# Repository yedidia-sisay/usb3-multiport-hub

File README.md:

# usb3-multiport-hub

An open-source USB 3.2 Gen 2 (10 Gbps) multiport hub & docking station — designed in KiCad 10.

## Overview

A compact (93 × 69 mm), 6-layer PCB that combines a high-speed USB hub, video output, and a card reader into a single board. Powered by a 12V DC input with an onboard 20A buck converter.

### Features

| Feature | Details |
|---|---|
| **Hub IC** | Microchip USB7216CT — USB 3.2 Gen 2 SmartHub, 10 Gbps |
| **Upstream** | USB Type-C with HD3SS3220 CC controller & 10G mux |
| **Downstream Port 1** | USB Type-C (10 Gbps + USB 2.0) |
| **Downstream Port 2** | USB 3.0 Type-A (10 Gbps + USB 2.0) |
| **SD Card Reader** | MicroSD/TF via Genesys Logic GL3224 |
| **HDMI Output** | USB 3.0 → HDMI via MacroSilicon MS9132 + 64Mbit SPI Flash |
| **Power Input** | 12V DC barrel jack (5.5 × 2.1 mm) |
| **ESD Protection** | TI TPD4E05U06 & TPD4E02B04 on all external ports |
| **PCB** | 6-layer, 93 × 69 mm, controlled impedance (90Ω USB, 100Ω HDMI) |

## Block Diagram

```
                    ┌──────────────────────────────────────┐
                    │         Microchip USB7216CT          │
  USB-C ─── HD3SS3220 ──▶ Upstream                        │
  (10G Mux)         │                                      │
                    │   Port 1 ──▶ USB-C Downstream        │
                    │   Port 2 ──▶ USB-A 3.0 Downstream    │
                    │   Port 3 ──▶ GL3224 ──▶ MicroSD Slot │
                    │   Port 4 ──▶ MS9132 ──▶ HDMI Output  │
                    └──────────────────────────────────────┘

  12V DC ──▶ TPS53353 (20A Buck) ──▶ +5V ──┬──▶ SGM61020 ──▶ +3.3V
                                            ├──▶ SGM61020 ──▶ +1.15V
                                            └──▶ TPS79325 ──▶ +2.5V (LDO)
```

## Schematic Hierarchy

| Sheet | Description |
|---|---|
| `usb_hub_2.kicad_sch` | Top-level sheet with hierarchy |
| `hub.kicad_sch` | USB7216 hub IC, crystal, decoupling |
| `upport.kicad_sch` | Upstream USB-C port with HD3SS3220 mux |
| `PORT1.kicad_sch` | Downstream USB-C port 1 |
| `port23.kicad_sch` | Downstream USB-A port 2 + GL3224 SD card reader |
| `port_4_5.kicad_sch` | MS9132 HDMI output + SPI flash |
| `power.kicad_sch` | Full power tree (12V → 5V/3.3V/1.15V/2.5V) |

## Key Components

| Part | Manufacturer | Description |
|---|---|---|
| USB7216CT/KDX | Microchip | USB 3.2 Gen 2 10Gbps SmartHub (VQFN-100) |
| HD3SS3220RNHR | Texas Instruments | USB-C DRP controller + 10G mux (WQFN-30) |
| GL3224-OIY04 | Genesys Logic | USB 3.0 SD/MMC card reader (QFN-64) |
| MS9132 | MacroSilicon | USB 3.0 → HDMI display adapter (QFN-64) |
| W25Q64JVSSIQ | Winbond | 64Mbit SPI Flash for MS9132 firmware |
| TPS53353DQPR | Texas Instruments | 20A synchronous buck converter, 12V→5V |
| SGM61020XN5G/TR | SG Micro | 2A synchronous buck converter (×2) |
| TPS79325DBVR | Texas Instruments | 200mA ultra-low-noise 2.5V LDO |
| AON7405 | Alpha & Omega Semi | 30V P-MOSFET for reverse polarity protection |
| AP22615BWU-7 | Diodes Inc | USB power distribution switch (×2) |
| TPD4E05U06 / TPD4E02B04 | Texas Instruments | 4-ch ultra-low capacitance ESD protection |

## PCB Stackup

| Layer | Function |
|---|---|
| L1 — F.Cu | Top signal (high-speed differential pairs) |
| L2 — In1.Cu | Solid GND reference plane |
| L3 — In2.Cu | Internal signal routing |
| L4 — In3.Cu | Power planes (+5V, +12V, +3.3V) |
| L5 — In4.Cu | GND plane |
| L6 — B.Cu | Bottom signal |

**Impedance-controlled netclasses:**
- `USB_90R` — 90 Ω differential (0.136 mm trace / 0.15 mm gap)
- `HDMI_100R` — 100 Ω differential (0.09 mm trace / 0.09 mm gap)
- `CLOCK` — 0.15 mm trace, 0.30 mm clearance
- `POWER` — 0.50 mm trace

## Repository Structure

```
usb3-multiport-hub/
├── usb_hub_2.kicad_pro          # KiCad project file
├── usb_hub_2.kicad_sch          # Top-level schematic
├── usb_hub_2.kicad_pcb          # PCB layout
├── usb_hub_2.kicad_dru          # Design rules
├── hub.kicad_sch                # Hub IC sheet
├── upport.kicad_sch             # Upstream USB-C port sheet
├── PORT1.kicad_sch              # Downstream USB-C port sheet
├── port23.kicad_sch             # Downstream USB-A + SD reader sheet
├── port_4_5.kicad_sch           # HDMI output sheet
├── power.kicad_sch              # Power supply sheet
├── custom_libs/
│   ├── local_parts.kicad_sym    # Custom schematic symbols
│   ├── local_parts.pretty/      # Custom PCB footprints (25)
│   └── local_parts.3dshapes/    # 3D models (STEP + WRL)
├── docs/                        # Datasheets & reference designs
├── images/                      # Board renders & schematics
└── output/                      # Manufacturing outputs (gerbers, BOM)
```

## Getting Started

### Opening the Project

1. Clone this repository
2. Open `usb_hub_2.kicad_pro` in KiCad
3. All custom libraries are project-relative — no additional library setup needed

### Manufacturing

The board is designed for standard 6-layer PCB fabrication with controlled impedance. Export Gerbers and drill files from KiCad to the `output/` directory.

## Design References

The `docs/` directory contains the key reference documents used during design:

- **USB7216 Datasheet** (DS00003143B)
- **USB7216 Hardware Design Checklist** (AN3286)
- **USB72x6 / USB7252 Errata** (80000847C)
- **USB7216 Evaluation Board Schematic**

## Status

> **⚠️ Work in Progress** — This design is under active development. DRC cleanup and manufacturing output generation are pending.

## License

This project is open-source hardware. See [LICENSE](LICENSE) for details.

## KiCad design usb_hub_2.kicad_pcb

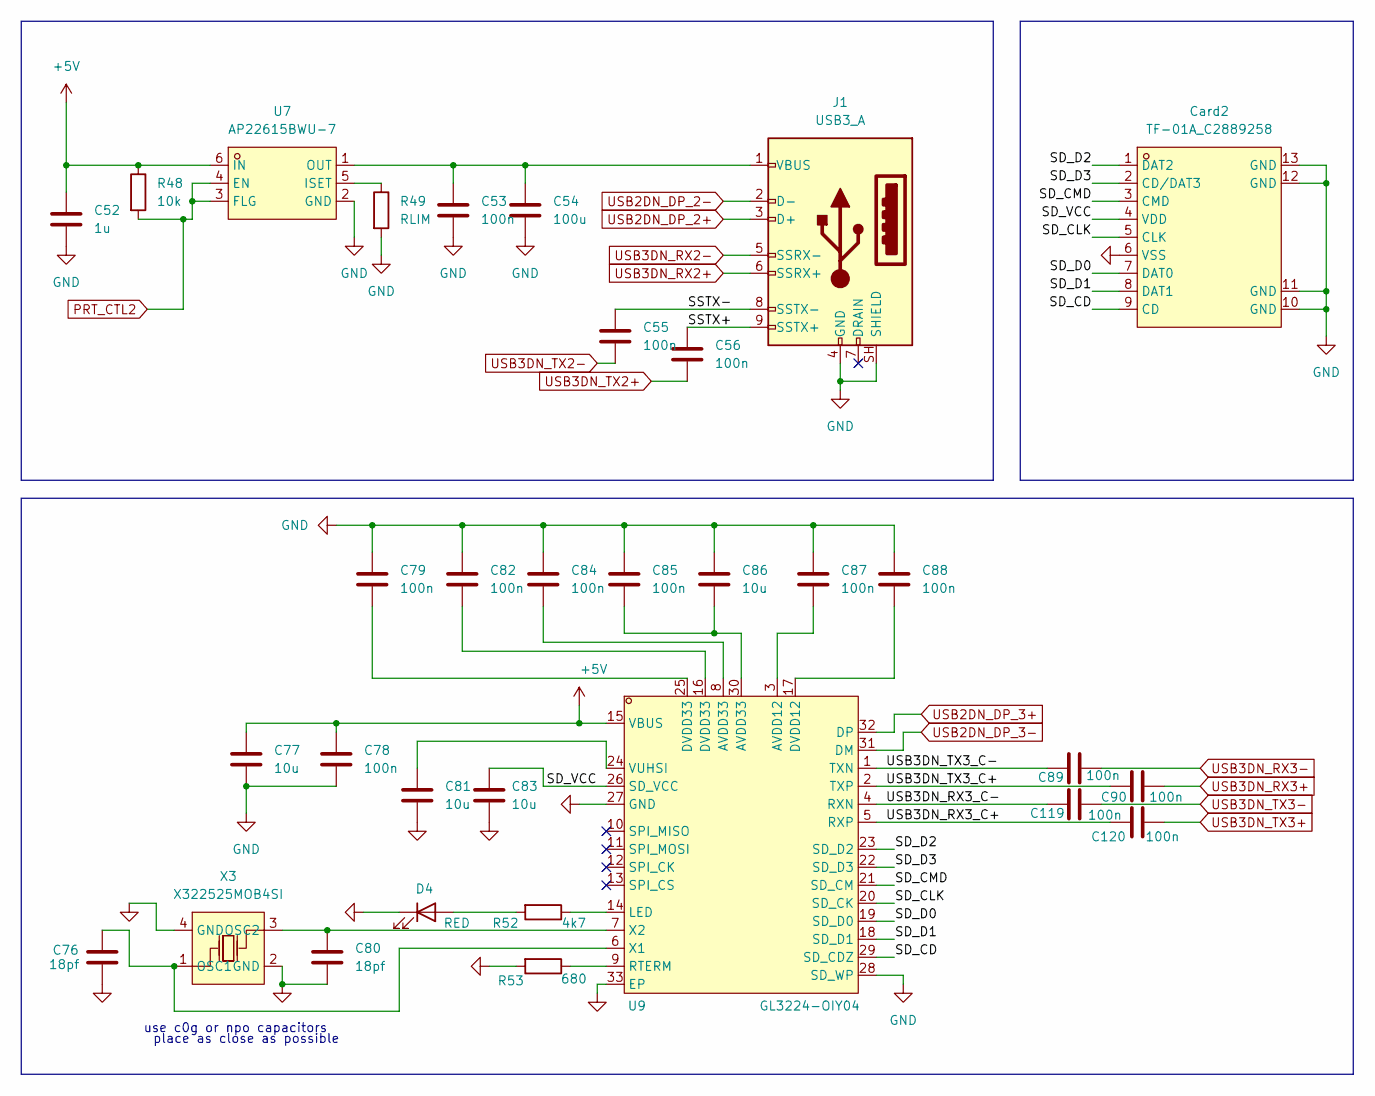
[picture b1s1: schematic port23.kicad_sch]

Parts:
C52: 1u; C_0402_1005Metric
C53, C55, C56, C78, C79, C82, C84, C85, C87, C88, C89, C90, C119, C120: 100n; C_0402_1005Metric
C54: 100u; C_0402_1005Metric
C76, C80: 18pf; C_0402_1005Metric
C77: 10u; C_0805_2012Metric
C81, C83, C86: 10u; C_0402_1005Metric
Card2: TF-01A_C2889258; TF-SMD_TF-02; MPN TF-01A; LCSC Part C2889258
D4: RED; LED_0402_1005Metric
J1: USB3_A; USB3_A_Receptacle_Wuerth_692122030100
R48: 10k; R_0402_1005Metric
R49: RLIM; R_0402_1005Metric
R52: 4k7; R_0402_1005Metric
R53: 680; R_0402_1005Metric
U7: AP22615BWU-7; TSOT-26_L2.9-W1.6-P0.95-LS2.8-BL; MPN AP22615BWU-7; LCSC Part C2150284
U9: GL3224-OIY04; HQFN-32_L5.0-W5.0-P0.50-BL-EP3.0; MPN GL3224-OIY04; LCSC Part C157357
X3: X322525MOB4SI; CRYSTAL-SMD_4P-L3.2-W2.5-BL; MPN X322525MOB4SI; LCSC Part C9006

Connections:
+5V: C52.1, C77.2, C78.2, R48.1, U7.6 (IN), U9.15 (VBUS); also elsewhere on the board
/PORT23/SD_CD: Card2.9 (CD), U9.29 (SD_CDZ)
/PORT23/SD_CLK: Card2.5 (CLK), U9.20 (SD_CK)
/PORT23/SD_CMD: Card2.3 (CMD), U9.21 (SD_CM)
/PORT23/SD_D0: Card2.7 (DAT0), U9.19 (SD_D0)
/PORT23/SD_D1: Card2.8 (DAT1), U9.18 (SD_D1)
/PORT23/SD_D2: Card2.1 (DAT2), U9.23 (SD_D2)
/PORT23/SD_D3: Card2.2 (CD/DAT3), U9.22 (SD_D3)
/PORT23/SD_VCC: C83.2, Card2.4 (VDD), U9.26 (SD_VCC)
/PORT23/SSTX+: C56.1, J1.9 (SSTX+)
/PORT23/SSTX-: C55.1, J1.8 (SSTX-)
/PORT23/USB3DN_RX3_C+: C120.1, U9.5 (RXP)
/PORT23/USB3DN_RX3_C-: C119.1, U9.4 (RXN)
/PORT23/USB3DN_TX3_C+: C90.1, U9.2 (TXP)
/PORT23/USB3DN_TX3_C-: C89.1, U9.1 (TXN)
GND: C52.2, C53.2, C54.2, C76.2, C77.1, C78.1, C79.2, C80.2, C81.1, C82.2, C83.1, C84.2, C85.2, C86.2, C87.2, C88.2, Card2.6 (VSS), Card2.10 (GND), Card2.11 (GND), Card2.12 (GND), Card2.13 (GND), D4.1 (K), J1.4 (GND), J1.SH (SHIELD), R49.2, R53.2, U7.2 (GND), U9.27 (GND), U9.28 (SD_WP), U9.33 (EP), X3.2 (GND), X3.4 (GND); also elsewhere on the board
unnamed: C79.1, U9.25 (DVDD33)
unnamed: C82.1, U9.16 (DVDD33)
unnamed: C84.1, U9.8 (AVDD33)
unnamed: C85.1, C86.1, U9.30 (AVDD33)
unnamed: D4.2 (A), R52.2
unnamed: C53.1, C54.1, J1.1 (VBUS), U7.1 (OUT)
unnamed: R49.1, U7.5 (ISET)
unnamed: C87.1, U9.3 (AVDD12)
unnamed: C88.1, U9.17 (DVDD12)
unnamed: R52.1, U9.14 (LED)
unnamed: R53.1, U9.9 (RTERM)
unnamed: C81.2, U9.24 (VUHSI)
unnamed: C76.1, U9.6 (X1), X3.1 (OSC1)
unnamed: C80.1, U9.7 (X2), X3.3 (OSC2)
PRT_CTL2: R48.2, U7.3 (FLG), U7.4 (EN); also elsewhere on the board
USB2DN_DP_2+: J1.3 (D+); also elsewhere on the board
USB2DN_DP_2-: J1.2 (D-); also elsewhere on the board
USB2DN_DP_3+: U9.32 (DP); also elsewhere on the board
USB2DN_DP_3-: U9.31 (DM); also elsewhere on the board
USB3DN_RX2+: J1.6 (SSRX+); also elsewhere on the board
USB3DN_RX2-: J1.5 (SSRX-); also elsewhere on the board
USB3DN_RX3+: C90.2; also elsewhere on the board
USB3DN_RX3-: C89.2; also elsewhere on the board
USB3DN_TX2+: C56.2; also elsewhere on the board
USB3DN_TX2-: C55.2; also elsewhere on the board
USB3DN_TX3+: C120.2; also elsewhere on the board
USB3DN_TX3-: C119.2; also elsewhere on the board

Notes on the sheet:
place as close as possible
use c0g or npo capacitors

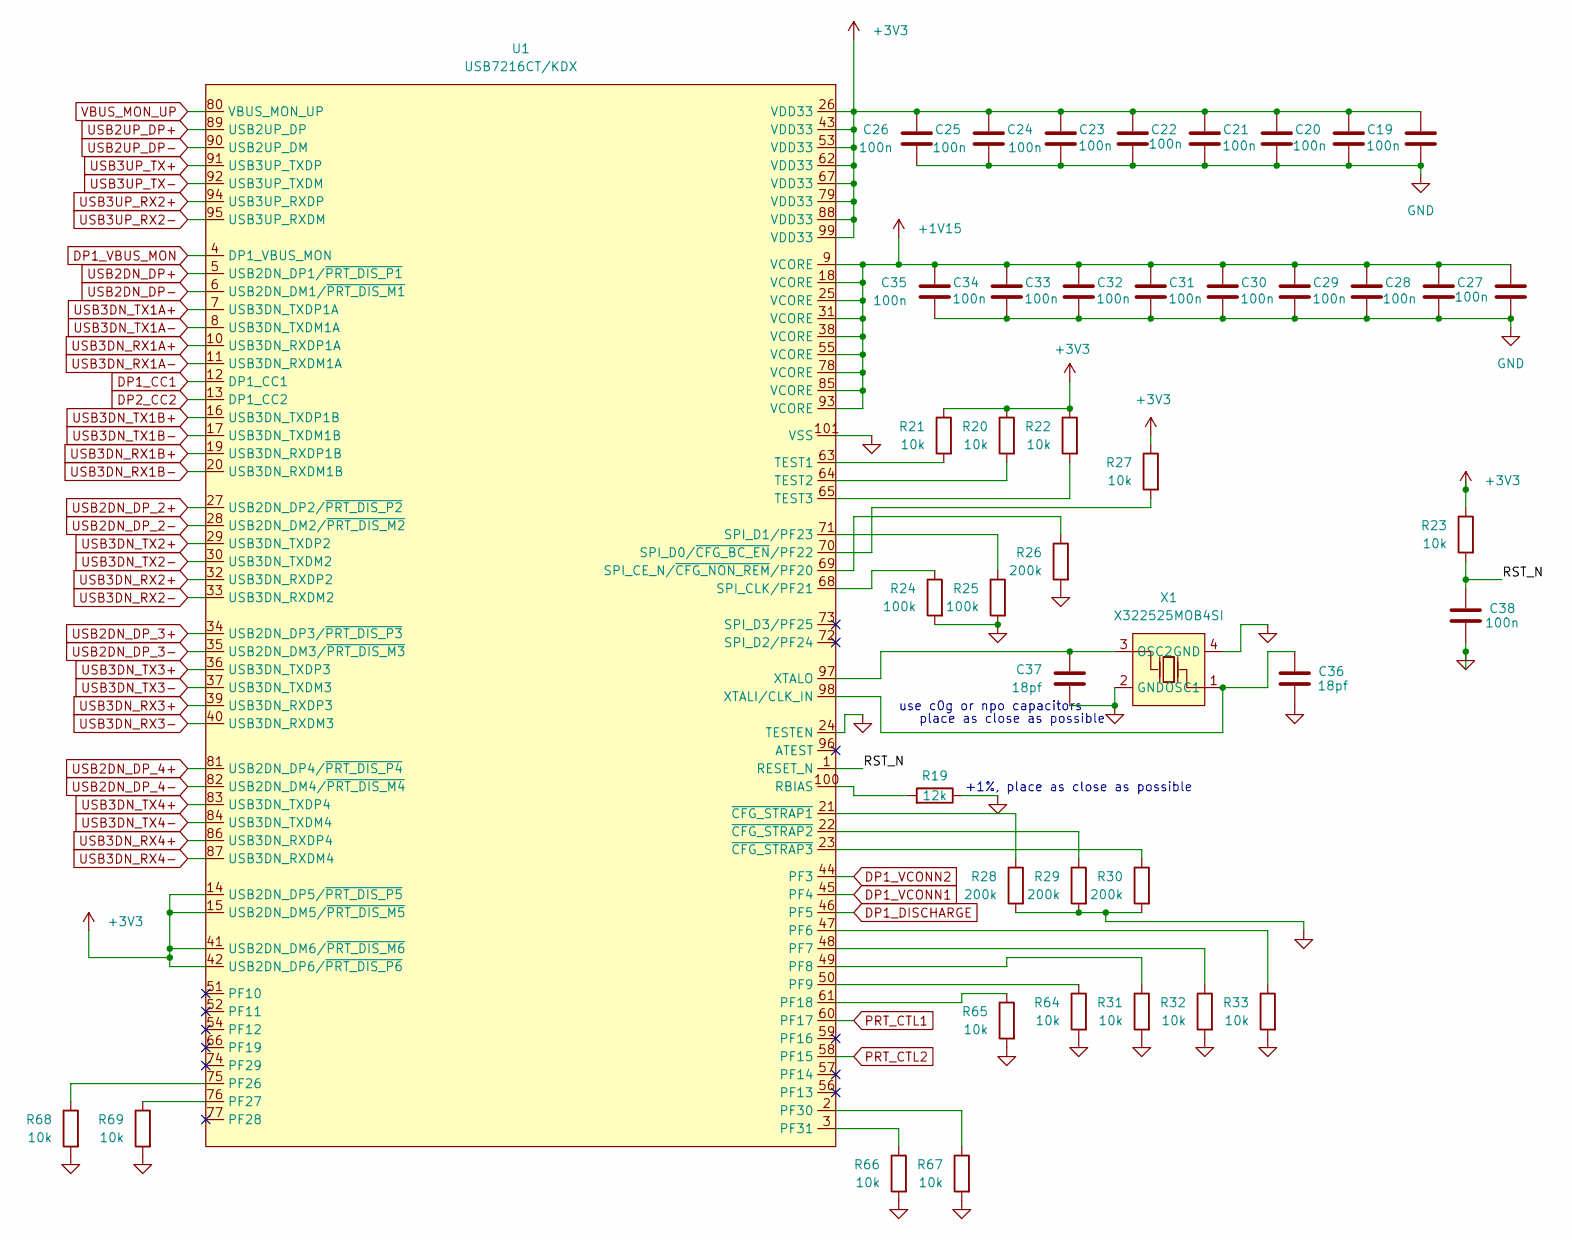
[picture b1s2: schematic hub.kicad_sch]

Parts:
C19, C20, C21, C22, C23, C24, C25, C26, C27, C28, C29, C30, C31, C32, C33, C34, C35, C38: 100n; C_0402_1005Metric
C36, C37: 18pf; C_0402_1005Metric
R19: 12k; R_0402_1005Metric
R20, R21, R22, R23, R27, R31, R32, R33, R64, R65, R66, R67, R68, R69: 10k; R_0402_1005Metric
R24, R25: 100k; R_0402_1005Metric
R26, R28, R29, R30: 200k; R_0402_1005Metric
U1: USB7216CT/KDX; VQFN-100_L12.0-W12.0-P0.40-TL-EP8.0; MPN USB7216CT/KDX; LCSC Part C3210684
X1: X322525MOB4SI; CRYSTAL-SMD_4P-L3.2-W2.5-BL; MPN X322525MOB4SI; LCSC Part C9006

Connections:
+1V15: C27.1, C28.1, C29.1, C30.1, C31.1, C32.1, C33.1, C34.1, C35.1, U1.9 (VCORE), U1.18 (VCORE), U1.25 (VCORE), U1.31 (VCORE), U1.38 (VCORE), U1.55 (VCORE), U1.78 (VCORE), U1.85 (VCORE), U1.93 (VCORE); also elsewhere on the board
+3V3: C19.1, C20.1, C21.1, C22.1, C23.1, C24.1, C25.1, C26.1, R20.1, R21.1, R22.1, R23.1, R27.1, U1.14 (USB2DN_DP5/~PRT_DIS_P5), U1.15 (USB2DN_DM5/~PRT_DIS_M5), U1.26 (VDD33), U1.41 (USB2DN_DM6/~PRT_DIS_M6), U1.42 (USB2DN_DP6/~PRT_DIS_P6), U1.43 (VDD33), U1.53 (VDD33), U1.62 (VDD33), U1.67 (VDD33), U1.79 (VDD33), U1.88 (VDD33), U1.99 (VDD33); also elsewhere on the board
/HUB/RST_N: C38.1, R23.2, U1.1 (RESET_N)
DP1_CC1: U1.12 (DP1_CC1); also elsewhere on the board
DP1_DISCHARGE: U1.46 (PF5); also elsewhere on the board
DP1_VBUS_MON: U1.4 (DP1_VBUS_MON); also elsewhere on the board
DP1_VCONN1: U1.45 (PF4); also elsewhere on the board
DP1_VCONN2: U1.44 (PF3); also elsewhere on the board
DP2_CC2: U1.13 (DP1_CC2); also elsewhere on the board
GND: C19.2, C20.2, C21.2, C22.2, C23.2, C24.2, C25.2, C26.2, C27.2, C28.2, C29.2, C30.2, C31.2, C32.2, C33.2, C34.2, C35.2, C36.2, C37.2, C38.2, R19.1, R24.2, R25.2, R26.2, R28.2, R29.2, R30.2, R31.2, R32.2, R33.2, R64.2, R65.2, R66.2, R67.2, R68.2, R69.2, U1.24 (TESTEN), U1.101 (VSS), X1.2 (GND), X1.4 (GND); also elsewhere on the board
unnamed: R33.1, U1.47 (PF6)
unnamed: R32.1, U1.48 (PF7)
unnamed: R31.1, U1.49 (PF8)
unnamed: R64.1, U1.50 (PF9)
unnamed: R65.1, U1.61 (PF18)
unnamed: R68.1, U1.75 (PF26)
unnamed: R69.1, U1.76 (PF27)
unnamed: R67.1, U1.2 (PF30)
unnamed: R66.1, U1.3 (PF31)
unnamed: R19.2, U1.100 (RBIAS)
unnamed: R26.1, U1.69 (SPI_CE_N/~CFG_NON_REM/PF20)
unnamed: R24.1, U1.68 (SPI_CLK/PF21)
unnamed: R27.2, U1.70 (SPI_D0/~CFG_BC_EN/PF22)
unnamed: R25.1, U1.71 (SPI_D1/PF23)
unnamed: R21.2, U1.63 (TEST1)
unnamed: R20.2, U1.64 (TEST2)
unnamed: R22.2, U1.65 (TEST3)
unnamed: C36.1, U1.98 (XTALI/CLK_IN), X1.1 (OSC1)
unnamed: C37.1, U1.97 (XTALO), X1.3 (OSC2)
unnamed: R28.1, U1.21 (~CFG_STRAP1)
unnamed: R29.1, U1.22 (~CFG_STRAP2)
unnamed: R30.1, U1.23 (~CFG_STRAP3)
PRT_CTL1: U1.60 (PF17); also elsewhere on the board
PRT_CTL2: U1.58 (PF15); also elsewhere on the board
USB2DN_DP+: U1.5 (USB2DN_DP1/~PRT_DIS_P1); also elsewhere on the board
USB2DN_DP-: U1.6 (USB2DN_DM1/~PRT_DIS_M1); also elsewhere on the board
USB2DN_DP_2+: U1.27 (USB2DN_DP2/~PRT_DIS_P2); also elsewhere on the board
USB2DN_DP_2-: U1.28 (USB2DN_DM2/~PRT_DIS_M2); also elsewhere on the board
USB2DN_DP_3+: U1.34 (USB2DN_DP3/~PRT_DIS_P3); also elsewhere on the board
USB2DN_DP_3-: U1.35 (USB2DN_DM3/~PRT_DIS_M3); also elsewhere on the board
USB2DN_DP_4+: U1.81 (USB2DN_DP4/~PRT_DIS_P4); also elsewhere on the board
USB2DN_DP_4-: U1.82 (USB2DN_DM4/~PRT_DIS_M4); also elsewhere on the board
USB2UP_DP+: U1.89 (USB2UP_DP); also elsewhere on the board
USB2UP_DP-: U1.90 (USB2UP_DM); also elsewhere on the board
USB3DN_RX1A+: U1.10 (USB3DN_RXDP1A); also elsewhere on the board
USB3DN_RX1A-: U1.11 (USB3DN_RXDM1A); also elsewhere on the board
USB3DN_RX1B+: U1.19 (USB3DN_RXDP1B); also elsewhere on the board
USB3DN_RX1B-: U1.20 (USB3DN_RXDM1B); also elsewhere on the board
USB3DN_RX2+: U1.32 (USB3DN_RXDP2); also elsewhere on the board
USB3DN_RX2-: U1.33 (USB3DN_RXDM2); also elsewhere on the board
USB3DN_RX3+: U1.39 (USB3DN_RXDP3); also elsewhere on the board
USB3DN_RX3-: U1.40 (USB3DN_RXDM3); also elsewhere on the board
USB3DN_RX4+: U1.86 (USB3DN_RXDP4); also elsewhere on the board
USB3DN_RX4-: U1.87 (USB3DN_RXDM4); also elsewhere on the board
USB3DN_TX1A+: U1.7 (USB3DN_TXDP1A); also elsewhere on the board
USB3DN_TX1A-: U1.8 (USB3DN_TXDM1A); also elsewhere on the board
USB3DN_TX1B+: U1.16 (USB3DN_TXDP1B); also elsewhere on the board
USB3DN_TX1B-: U1.17 (USB3DN_TXDM1B); also elsewhere on the board
USB3DN_TX2+: U1.29 (USB3DN_TXDP2); also elsewhere on the board
USB3DN_TX2-: U1.30 (USB3DN_TXDM2); also elsewhere on the board
USB3DN_TX3+: U1.36 (USB3DN_TXDP3); also elsewhere on the board
USB3DN_TX3-: U1.37 (USB3DN_TXDM3); also elsewhere on the board
USB3DN_TX4+: U1.83 (USB3DN_TXDP4); also elsewhere on the board
USB3DN_TX4-: U1.84 (USB3DN_TXDM4); also elsewhere on the board
USB3UP_RX2+: U1.94 (USB3UP_RXDP); also elsewhere on the board
USB3UP_RX2-: U1.95 (USB3UP_RXDM); also elsewhere on the board
USB3UP_TX+: U1.91 (USB3UP_TXDP); also elsewhere on the board
USB3UP_TX-: U1.92 (USB3UP_TXDM); also elsewhere on the board
VBUS_MON_UP: U1.80 (VBUS_MON_UP); also elsewhere on the board

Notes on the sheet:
+1%, place as close as possible
place as close as possible
use c0g or npo capacitors

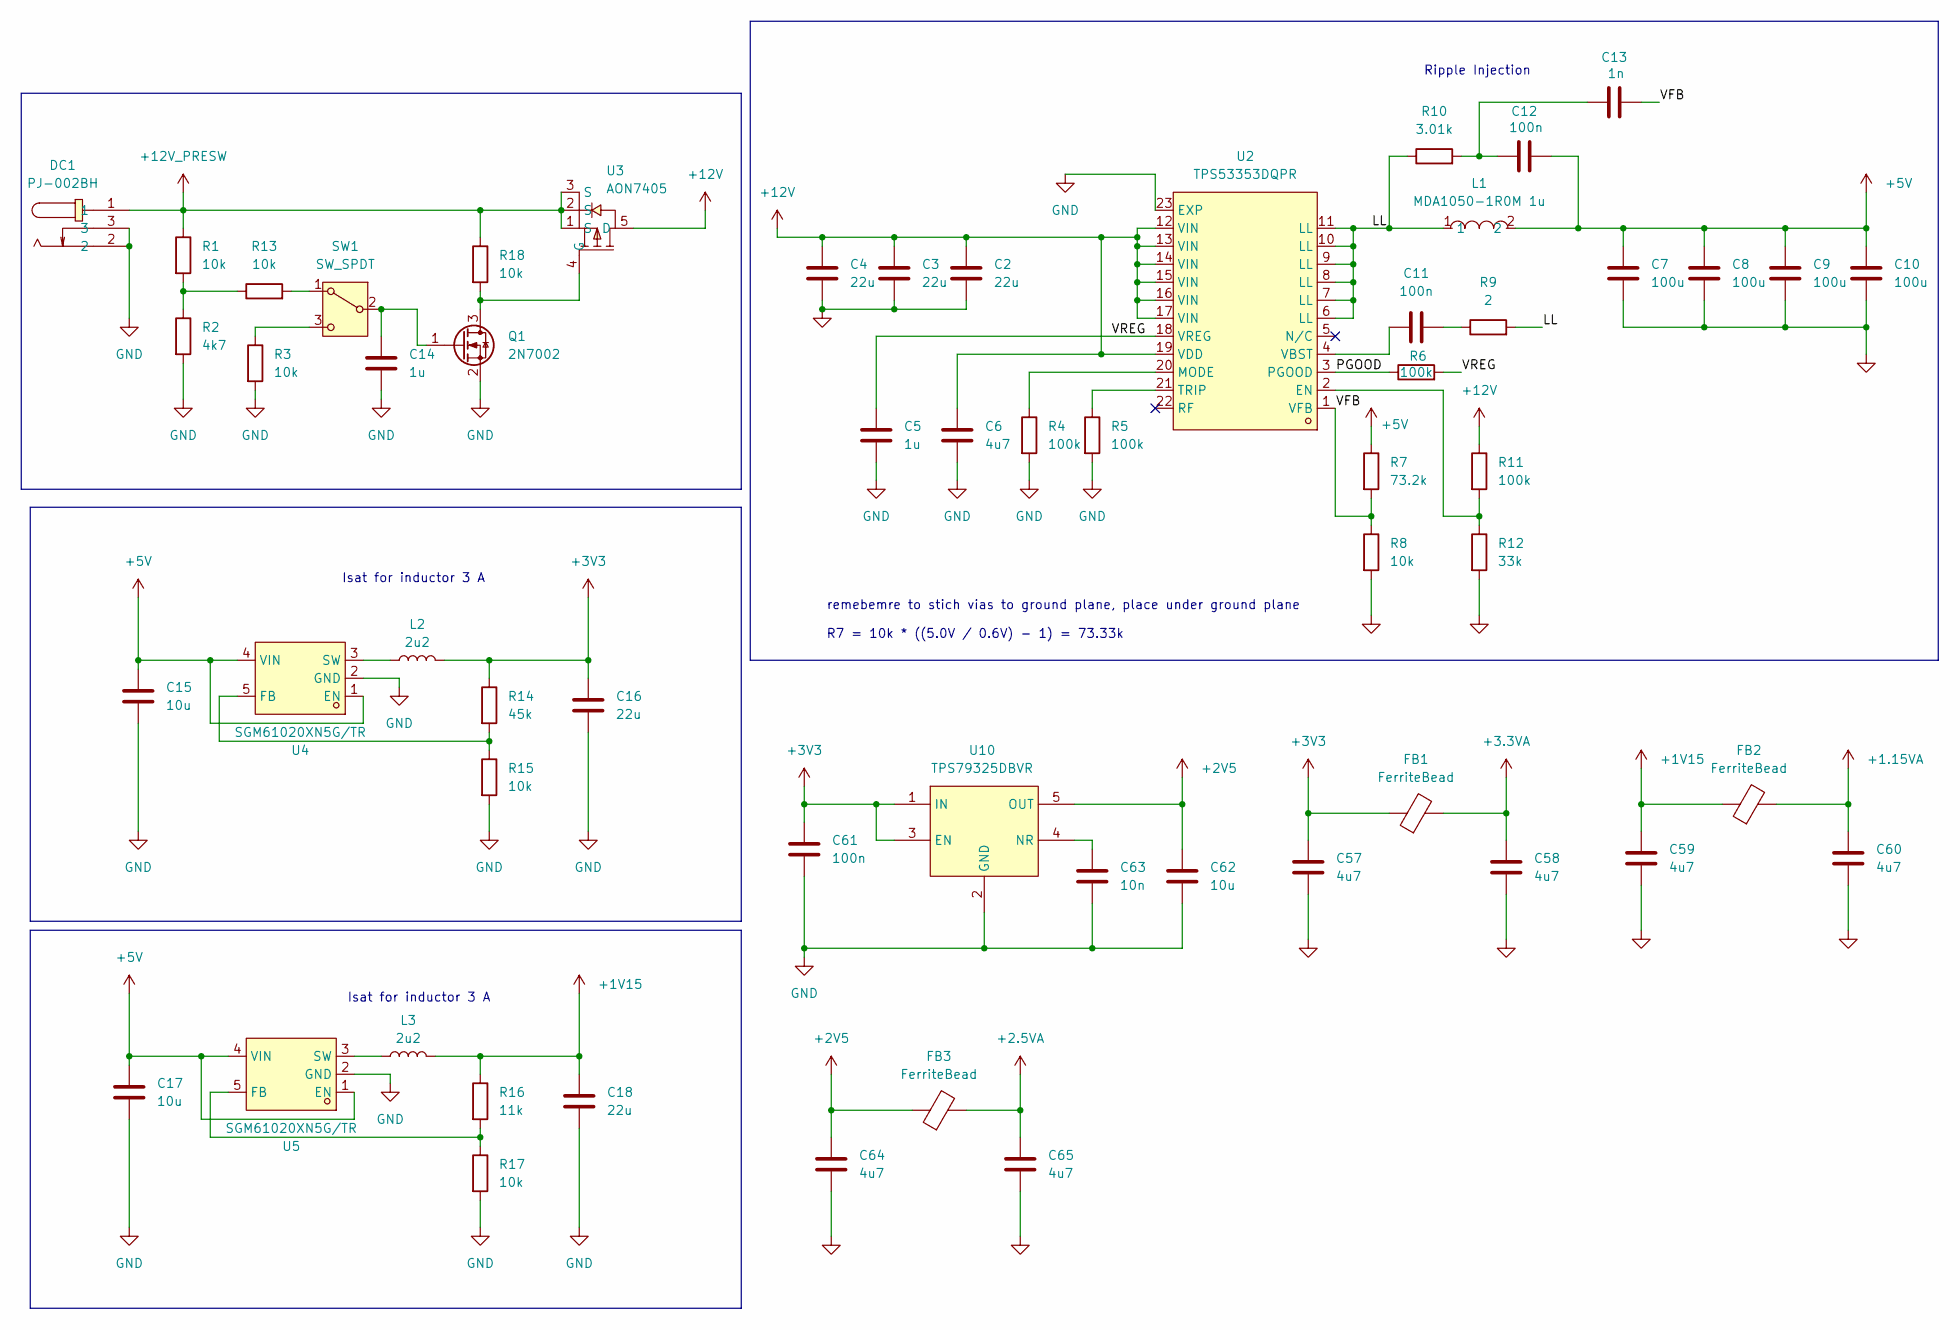
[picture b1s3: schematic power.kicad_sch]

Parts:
C2, C3, C4: 22u; C_1210_3225Metric
C5, C14: 1u; C_0402_1005Metric
C6, C57, C58, C59, C60, C64, C65: 4u7; C_0402_1005Metric
C7, C8, C9, C10: 100u; C_0603_1608Metric
C11, C12, C61: 100n; C_0402_1005Metric
C13: 1n; C_0402_1005Metric
C15, C17, C62: 10u; C_0805_2012Metric
C16, C18: 22u; C_0805_2012Metric
C63: 10n; C_0402_1005Metric
DC1: PJ-002BH; DC-IN-TH_PJ-002BH; MPN PJ-002BH; LCSC Part C22359705
FB1, FB2, FB3: FerriteBead; L_0402_1005Metric
L1: MDA1050-1R0M 1u; IND-SMD_L10.0-W10.0_MDA1050-3R3M; MPN MDA1050-1R0M; LCSC Part C2847558
L2, L3: 2u2; L_1008_2520Metric
Q1: 2N7002; SOT-23
R1, R3, R8, R13, R15, R17, R18: 10k; R_0402_1005Metric
R2: 4k7; R_0402_1005Metric
R4, R5, R6, R11: 100k; R_0402_1005Metric
R7: 73.2k; R_0402_1005Metric
R9: 2; R_0402_1005Metric
R10: 3.01k; R_0402_1005Metric
R12: 33k; R_0402_1005Metric
R14: 45k; R_0402_1005Metric
R16: 11k; R_0402_1005Metric
SW1: SW_SPDT; SW_SPDT_PCM12
U2: TPS53353DQPR; LSON-CLIP-22_L6.0-W5.0-P0.50-BL-EP; MPN TPS53353DQPR; LCSC Part C143959
U3: AON7405; PDFN-8_L3.0-W3.0-P0.65-LS3.3-BL; MPN AON7405; LCSC Part C41348137
U4, U5: SGM61020XN5G/TR; SOT-23-5_L2.9-W1.6-P0.95-LS2.8-BL; MPN SGM61020XN5G/TR; LCSC Part C5153643
U10: TPS79325DBVR; SOT-23-5_L3.0-W1.7-P0.95-LS2.8-BR; MPN TPS79325DBVR; LCSC Part C14596

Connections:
+1.15VA: C60.1, FB2.2; also elsewhere on the board
+1V15: C18.1, C59.1, FB2.1, L3.2, R16.1; also elsewhere on the board
+2.5VA: C65.1, FB3.2; also elsewhere on the board
+2V5: C62.1, C64.1, FB3.1, U10.5 (OUT)
+3.3VA: C58.1, FB1.2; also elsewhere on the board
+3V3: C16.1, C57.1, C61.1, FB1.1, L2.2, R14.1, U10.1 (IN), U10.3 (EN); also elsewhere on the board
+5V: C7.1, C8.1, C9.1, C10.1, C12.1, C15.1, C17.1, L1.2, R7.1, U4.1 (EN), U4.4 (VIN), U5.1 (EN), U5.4 (VIN); also elsewhere on the board
+12V: C2.1, C3.1, C4.1, C6.1, R11.1, U2.12 (VIN), U2.13 (VIN), U2.14 (VIN), U2.15 (VIN), U2.16 (VIN), U2.17 (VIN), U2.19 (VDD), U3.5 (D)
+12V_PRESW: DC1.1, R1.1, R18.1, U3.1 (S), U3.2 (S), U3.3 (S)
/Power/LL: L1.1, R9.2, R10.1, U2.6 (LL), U2.7 (LL), U2.8 (LL), U2.9 (LL), U2.10 (LL), U2.11 (LL)
/Power/PGOOD: R6.1, U2.3 (PGOOD)
/Power/VFB: C13.1, R7.2, R8.1, U2.1 (VFB)
/Power/VREG: C5.1, R6.2, U2.18 (VREG)
GND: C2.2, C3.2, C4.2, C5.2, C6.2, C7.2, C8.2, C9.2, C10.2, C14.2, C15.2, C16.2, C17.2, C18.2, C57.2, C58.2, C59.2, C60.2, C61.2, C62.2, C63.2, C64.2, C65.2, DC1.2, DC1.3, Q1.2 (S), R2.2, R3.2, R4.2, R5.2, R8.2, R12.2, R15.2, R17.2, U2.23 (EXP), U4.2 (GND), U5.2 (GND), U10.2 (GND); also elsewhere on the board
unnamed: C11.1, R9.1
unnamed: C12.2, C13.2, R10.2
unnamed: Q1.3 (D), R18.2, U3.4 (G)
unnamed: C14.1, Q1.1 (G), SW1.2 (B)
unnamed: R1.2, R2.1, R13.1
unnamed: R13.2, SW1.1 (A)
unnamed: R3.1, SW1.3 (C)
unnamed: R11.2, R12.1, U2.2 (EN)
unnamed: R4.1, U2.20 (MODE)
unnamed: R5.1, U2.21 (TRIP)
unnamed: C11.2, U2.4 (VBST)
unnamed: R14.2, R15.1, U4.5 (FB)
unnamed: L2.1, U4.3 (SW)
unnamed: R16.2, R17.1, U5.5 (FB)
unnamed: L3.1, U5.3 (SW)
unnamed: C63.1, U10.4 (NR)

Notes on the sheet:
Ripple Injection
Isat for inductor 3 A
remebemre to stich vias to ground plane, place under ground plane
R7 = 10k * ((5.0V / 0.6V) - 1) = 73.33k

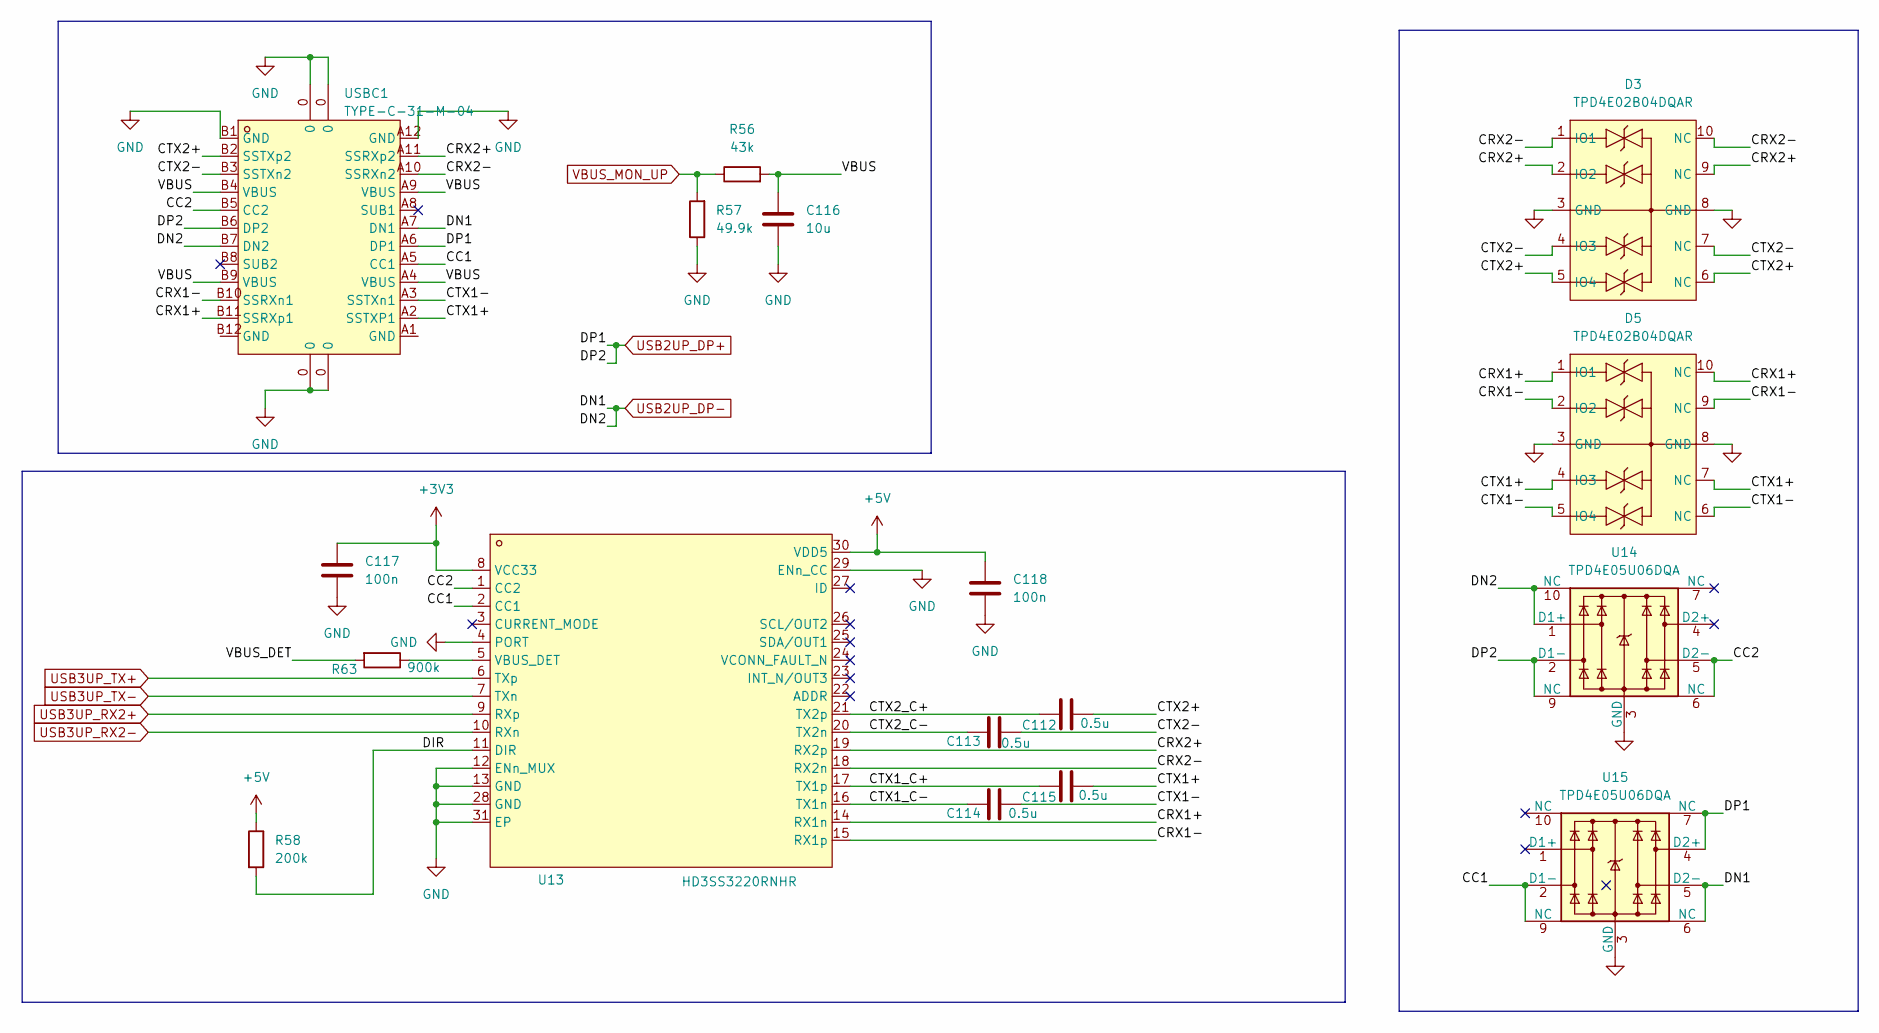
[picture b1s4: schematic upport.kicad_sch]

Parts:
C112, C113, C114, C115: 0.5u; C_0402_1005Metric
C116: 10u; C_0402_1005Metric
C117, C118: 100n; C_0402_1005Metric
D3, D5: TPD4E02B04DQAR; USON-10_L2.5-W1.0-P0.50-BL; MPN TPD4E02B04DQAR; LCSC Part C106794
R56: 43k; R_0402_1005Metric
R57: 49.9k; R_0402_1005Metric
R58: 200k; R_0402_1005Metric
R63: 900k; R_0402_1005Metric
U13: HD3SS3220RNHR; WQFN-30_L4.5-W2.5-P0.4-BL-EP; MPN HD3SS3220RNHR; LCSC Part C165155
U14, U15: TPD4E05U06DQA; USON-10_2.5x1.0mm_P0.5mm
USBC1: TYPE-C-31-M-04; USB-C-SMD_TYPE-C-USB-20; MPN TYPE-C-31-M-04; LCSC Part C129018

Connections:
+3V3: C117.1, U13.8 (VCC33); also elsewhere on the board
+5V: C118.1, R58.1, U13.30 (VDD5); also elsewhere on the board
/USB_C_UP_PORT/CC1: U13.2 (CC1), U15.2 (D1-), U15.9 (NC), USBC1.A5 (CC1)
/USB_C_UP_PORT/CC2: U13.1 (CC2), U14.5 (D2-), U14.6 (NC), USBC1.B5 (CC2)
/USB_C_UP_PORT/CRX1+: D5.1 (IO1), D5.10 (NC), U13.14 (RX1n), USBC1.B11 (SSRXp1)
/USB_C_UP_PORT/CRX1-: D5.2 (IO2), D5.9 (NC), U13.15 (RX1p), USBC1.B10 (SSRXn1)
/USB_C_UP_PORT/CRX2+: D3.2 (IO2), D3.9 (NC), U13.19 (RX2p), USBC1.A11 (SSRXp2)
/USB_C_UP_PORT/CRX2-: D3.1 (IO1), D3.10 (NC), U13.18 (RX2n), USBC1.A10 (SSRXn2)
/USB_C_UP_PORT/CTX1+: C115.2, D5.4 (IO3), D5.7 (NC), USBC1.A2 (SSTXP1)
/USB_C_UP_PORT/CTX1-: C114.2, D5.5 (IO4), D5.6 (NC), USBC1.A3 (SSTXn1)
/USB_C_UP_PORT/CTX1_C+: C115.1, U13.17 (TX1p)
/USB_C_UP_PORT/CTX1_C-: C114.1, U13.16 (TX1n)
/USB_C_UP_PORT/CTX2+: C112.2, D3.5 (IO4), D3.6 (NC), USBC1.B2 (SSTXp2)
/USB_C_UP_PORT/CTX2-: C113.2, D3.4 (IO3), D3.7 (NC), USBC1.B3 (SSTXn2)
/USB_C_UP_PORT/CTX2_C+: C112.1, U13.21 (TX2p)
/USB_C_UP_PORT/CTX2_C-: C113.1, U13.20 (TX2n)
/USB_C_UP_PORT/DIR: R58.2, U13.11 (DIR)
/USB_C_UP_PORT/VBUS: C116.1, R56.2, USBC1.A4 (VBUS), USBC1.A9 (VBUS), USBC1.B4 (VBUS), USBC1.B9 (VBUS)
/USB_C_UP_PORT/VBUS_DET: R63.2
GND: C116.2, C117.2, C118.2, D3.3 (GND), D3.8 (GND), D5.3 (GND), D5.8 (GND), R57.1, U13.4 (PORT), U13.12 (ENn_MUX), U13.13 (GND), U13.28 (GND), U13.29 (ENn_CC), U13.31 (EP), U14.3 (GND), U14.8 (GND), U15.3 (GND), U15.8 (GND), USBC1.0, USBC1.A12 (GND), USBC1.B1 (GND); also elsewhere on the board
unnamed: R63.1, U13.5 (VBUS_DET)
USB2UP_DP+: U14.2 (D1-), U14.9 (NC), U15.4 (D2+), U15.7 (NC), USBC1.A6 (DP1), USBC1.B6 (DP2); also elsewhere on the board
USB2UP_DP-: U14.1 (D1+), U14.10 (NC), U15.5 (D2-), U15.6 (NC), USBC1.A7 (DN1), USBC1.B7 (DN2); also elsewhere on the board
USB3UP_RX2+: U13.9 (RXp); also elsewhere on the board
USB3UP_RX2-: U13.10 (RXn); also elsewhere on the board
USB3UP_TX+: U13.6 (TXp); also elsewhere on the board
USB3UP_TX-: U13.7 (TXn); also elsewhere on the board
VBUS_MON_UP: R56.1, R57.2; also elsewhere on the board

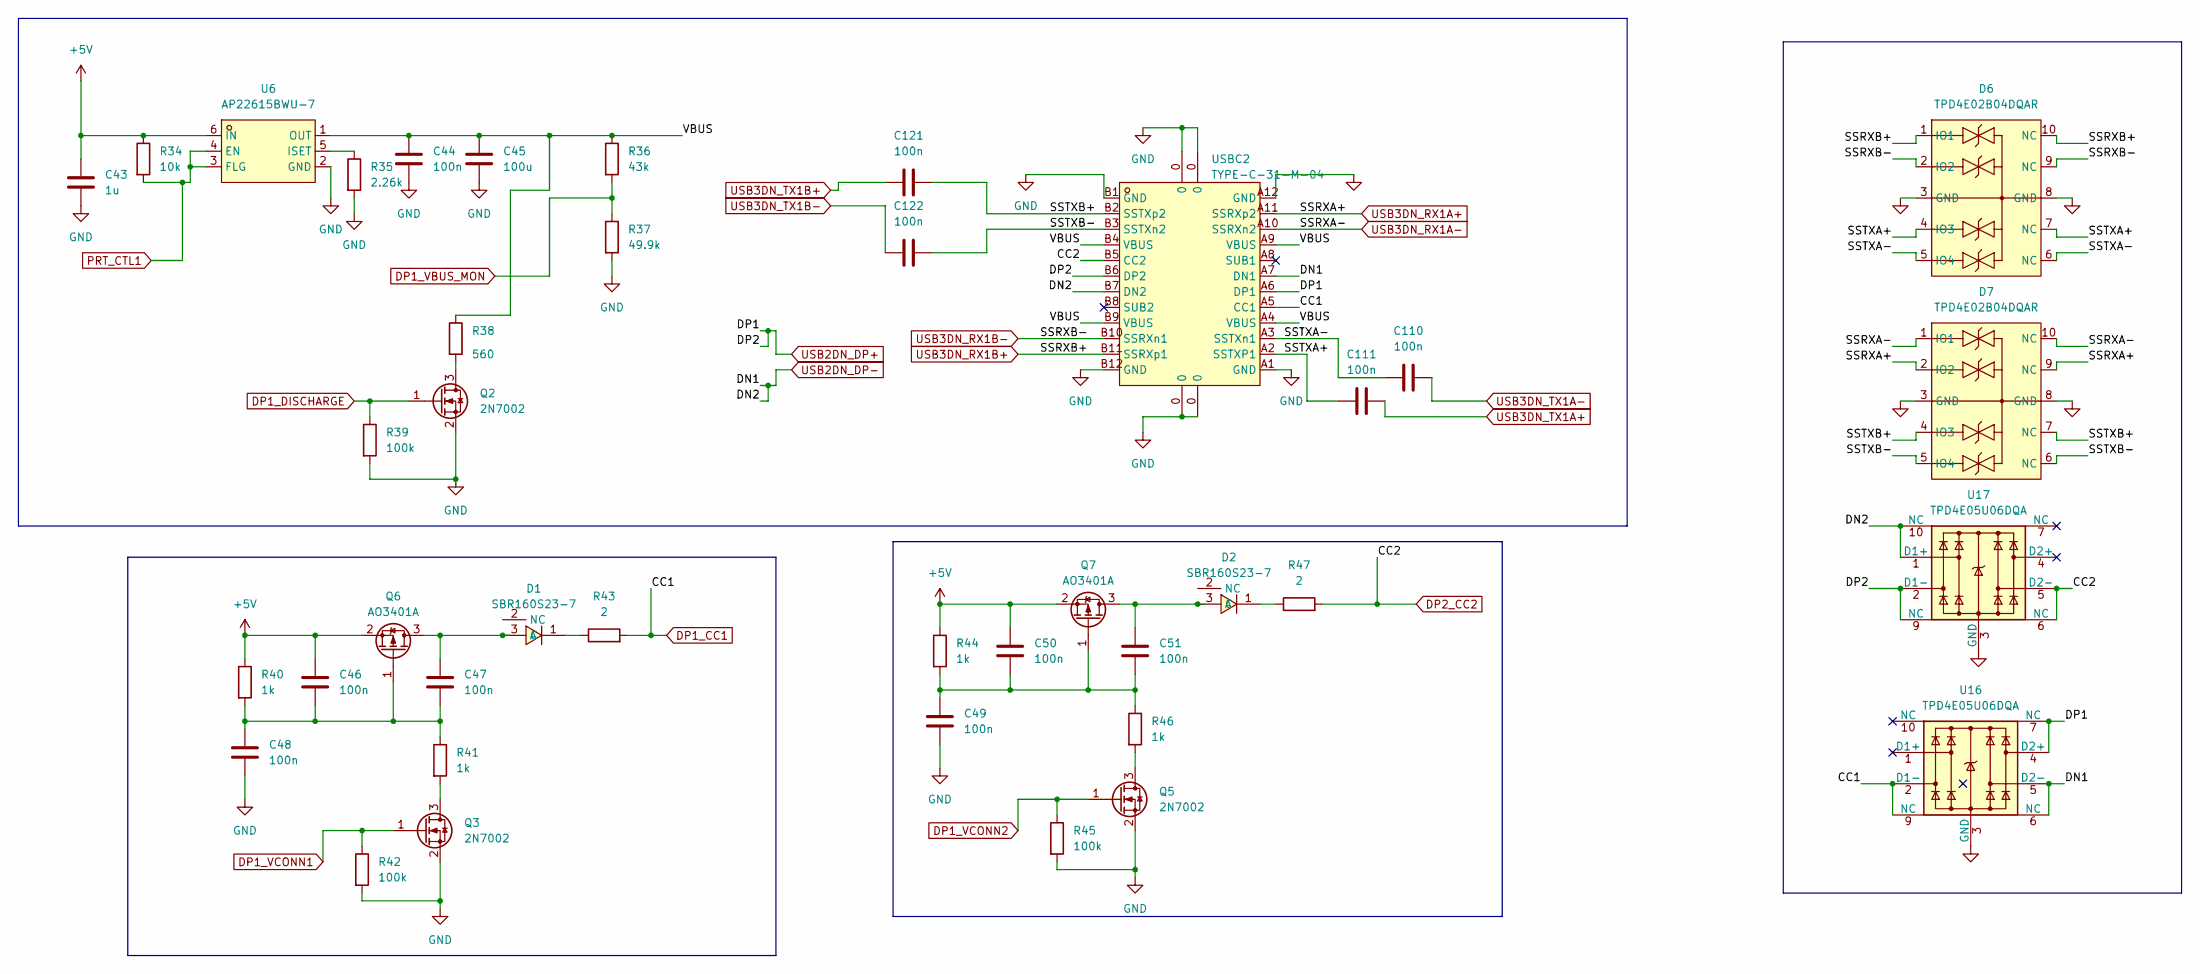
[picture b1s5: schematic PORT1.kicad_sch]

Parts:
C43: 1u; C_0402_1005Metric
C44, C46, C47, C48, C49, C50, C51, C110, C111, C121, C122: 100n; C_0402_1005Metric
C45: 100u; C_0402_1005Metric
D1, D2: SBR160S23-7; SOT-23-3_L2.9-W1.3-P1.83-LS2.4-BR; MPN SBR160S23-7; LCSC Part C154892
D6, D7: TPD4E02B04DQAR; USON-10_L2.5-W1.0-P0.50-BL; MPN TPD4E02B04DQAR; LCSC Part C106794
Q2, Q3, Q5: 2N7002; SOT-23
Q6, Q7: AO3401A; SOT-23
R34: 10k; R_0402_1005Metric
R35: 2.26k; R_0402_1005Metric
R36: 43k; R_0402_1005Metric
R37: 49.9k; R_0402_1005Metric
R38: 560; R_0402_1005Metric
R39, R42, R45: 100k; R_0402_1005Metric
R40, R41, R44, R46: 1k; R_0402_1005Metric
R43, R47: 2; R_0402_1005Metric
U6: AP22615BWU-7; TSOT-26_L2.9-W1.6-P0.95-LS2.8-BL; MPN AP22615BWU-7; LCSC Part C2150284
U16, U17: TPD4E05U06DQA; USON-10_2.5x1.0mm_P0.5mm
USBC2: TYPE-C-31-M-04; USB-C-SMD_TYPE-C-USB-20; MPN TYPE-C-31-M-04; LCSC Part C129018

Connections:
+5V: C43.1, C46.1, C50.1, Q6.2 (S), Q7.2 (S), R34.1, R40.1, R44.1, U6.6 (IN); also elsewhere on the board
/USB_DOWN_PORT1/SSTXA+: C111.2, D6.4 (IO3), D6.7 (NC), USBC2.A2 (SSTXP1)
/USB_DOWN_PORT1/SSTXA-: C110.2, D6.5 (IO4), D6.6 (NC), USBC2.A3 (SSTXn1)
/USB_DOWN_PORT1/SSTXB+: C121.1, D7.4 (IO3), D7.7 (NC), USBC2.B2 (SSTXp2)
/USB_DOWN_PORT1/SSTXB-: C122.1, D7.5 (IO4), D7.6 (NC), USBC2.B3 (SSTXn2)
/USB_DOWN_PORT1/VBUS: C44.1, C45.1, R36.1, R38.1, U6.1 (OUT), USBC2.A4 (VBUS), USBC2.A9 (VBUS), USBC2.B4 (VBUS), USBC2.B9 (VBUS)
DP1_CC1: R43.2, U16.2 (D1-), U16.9 (NC), USBC2.A5 (CC1); also elsewhere on the board
DP1_DISCHARGE: Q2.1 (G), R39.1; also elsewhere on the board
DP1_VBUS_MON: R36.2, R37.1; also elsewhere on the board
DP1_VCONN1: Q3.1 (G), R42.1; also elsewhere on the board
DP1_VCONN2: Q5.1 (G), R45.1; also elsewhere on the board
DP2_CC2: R47.2, U17.5 (D2-), U17.6 (NC), USBC2.B5 (CC2); also elsewhere on the board
GND: C43.2, C44.2, C45.2, C48.2, C49.2, D6.3 (GND), D6.8 (GND), D7.3 (GND), D7.8 (GND), Q2.2 (S), Q3.2 (S), Q5.2 (S), R35.2, R37.2, R39.2, R42.2, R45.2, U6.2 (GND), U16.3 (GND), U16.8 (GND), U17.3 (GND), U17.8 (GND), USBC2.0, USBC2.A1 (GND), USBC2.A12 (GND), USBC2.B1 (GND), USBC2.B12 (GND); also elsewhere on the board
unnamed: C47.1, D1.3 (A), Q6.3 (D)
unnamed: D1.1 (C), R43.1
unnamed: C51.1, D2.3 (A), Q7.3 (D)
unnamed: D2.1 (C), R47.1
unnamed: Q2.3 (D), R38.2
unnamed: Q3.3 (D), R41.2
unnamed: Q5.3 (D), R46.2
unnamed: C46.2, C47.2, C48.1, Q6.1 (G), R40.2, R41.1
unnamed: C49.1, C50.2, C51.2, Q7.1 (G), R44.2, R46.1
unnamed: R35.1, U6.5 (ISET)
PRT_CTL1: R34.2, U6.3 (FLG), U6.4 (EN); also elsewhere on the board
USB2DN_DP+: U16.4 (D2+), U16.7 (NC), U17.2 (D1-), U17.9 (NC), USBC2.A6 (DP1), USBC2.B6 (DP2); also elsewhere on the board
USB2DN_DP-: U16.5 (D2-), U16.6 (NC), U17.1 (D1+), U17.10 (NC), USBC2.A7 (DN1), USBC2.B7 (DN2); also elsewhere on the board
USB3DN_RX1A+: D7.2 (IO2), D7.9 (NC), USBC2.A11 (SSRXp2); also elsewhere on the board
USB3DN_RX1A-: D7.1 (IO1), D7.10 (NC), USBC2.A10 (SSRXn2); also elsewhere on the board
USB3DN_RX1B+: D6.1 (IO1), D6.10 (NC), USBC2.B11 (SSRXp1); also elsewhere on the board
USB3DN_RX1B-: D6.2 (IO2), D6.9 (NC), USBC2.B10 (SSRXn1); also elsewhere on the board
USB3DN_TX1A+: C111.1; also elsewhere on the board
USB3DN_TX1A-: C110.1; also elsewhere on the board
USB3DN_TX1B+: C121.2; also elsewhere on the board
USB3DN_TX1B-: C122.2; also elsewhere on the board
